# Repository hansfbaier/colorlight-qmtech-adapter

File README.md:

# colorlight-qmtech-adapter
Adapter to use Colorlight i5/i9 FPGA boards in a QMTech board form factor
This is the variant with Ethernet RJ45 connectors.

Please note:
* J1 Pin 8 is not length matched to the other Pins.
* J1 Pins 59 and 60 are not connected!

# Variants
* [With horizontal connector] (https://github.com/hansfbaier/colorlight-qmtech-adapter/)
* [With vertical connector] (https://github.com/hansfbaier/colorlight-qmtech-adapter/tree/upright-connector)

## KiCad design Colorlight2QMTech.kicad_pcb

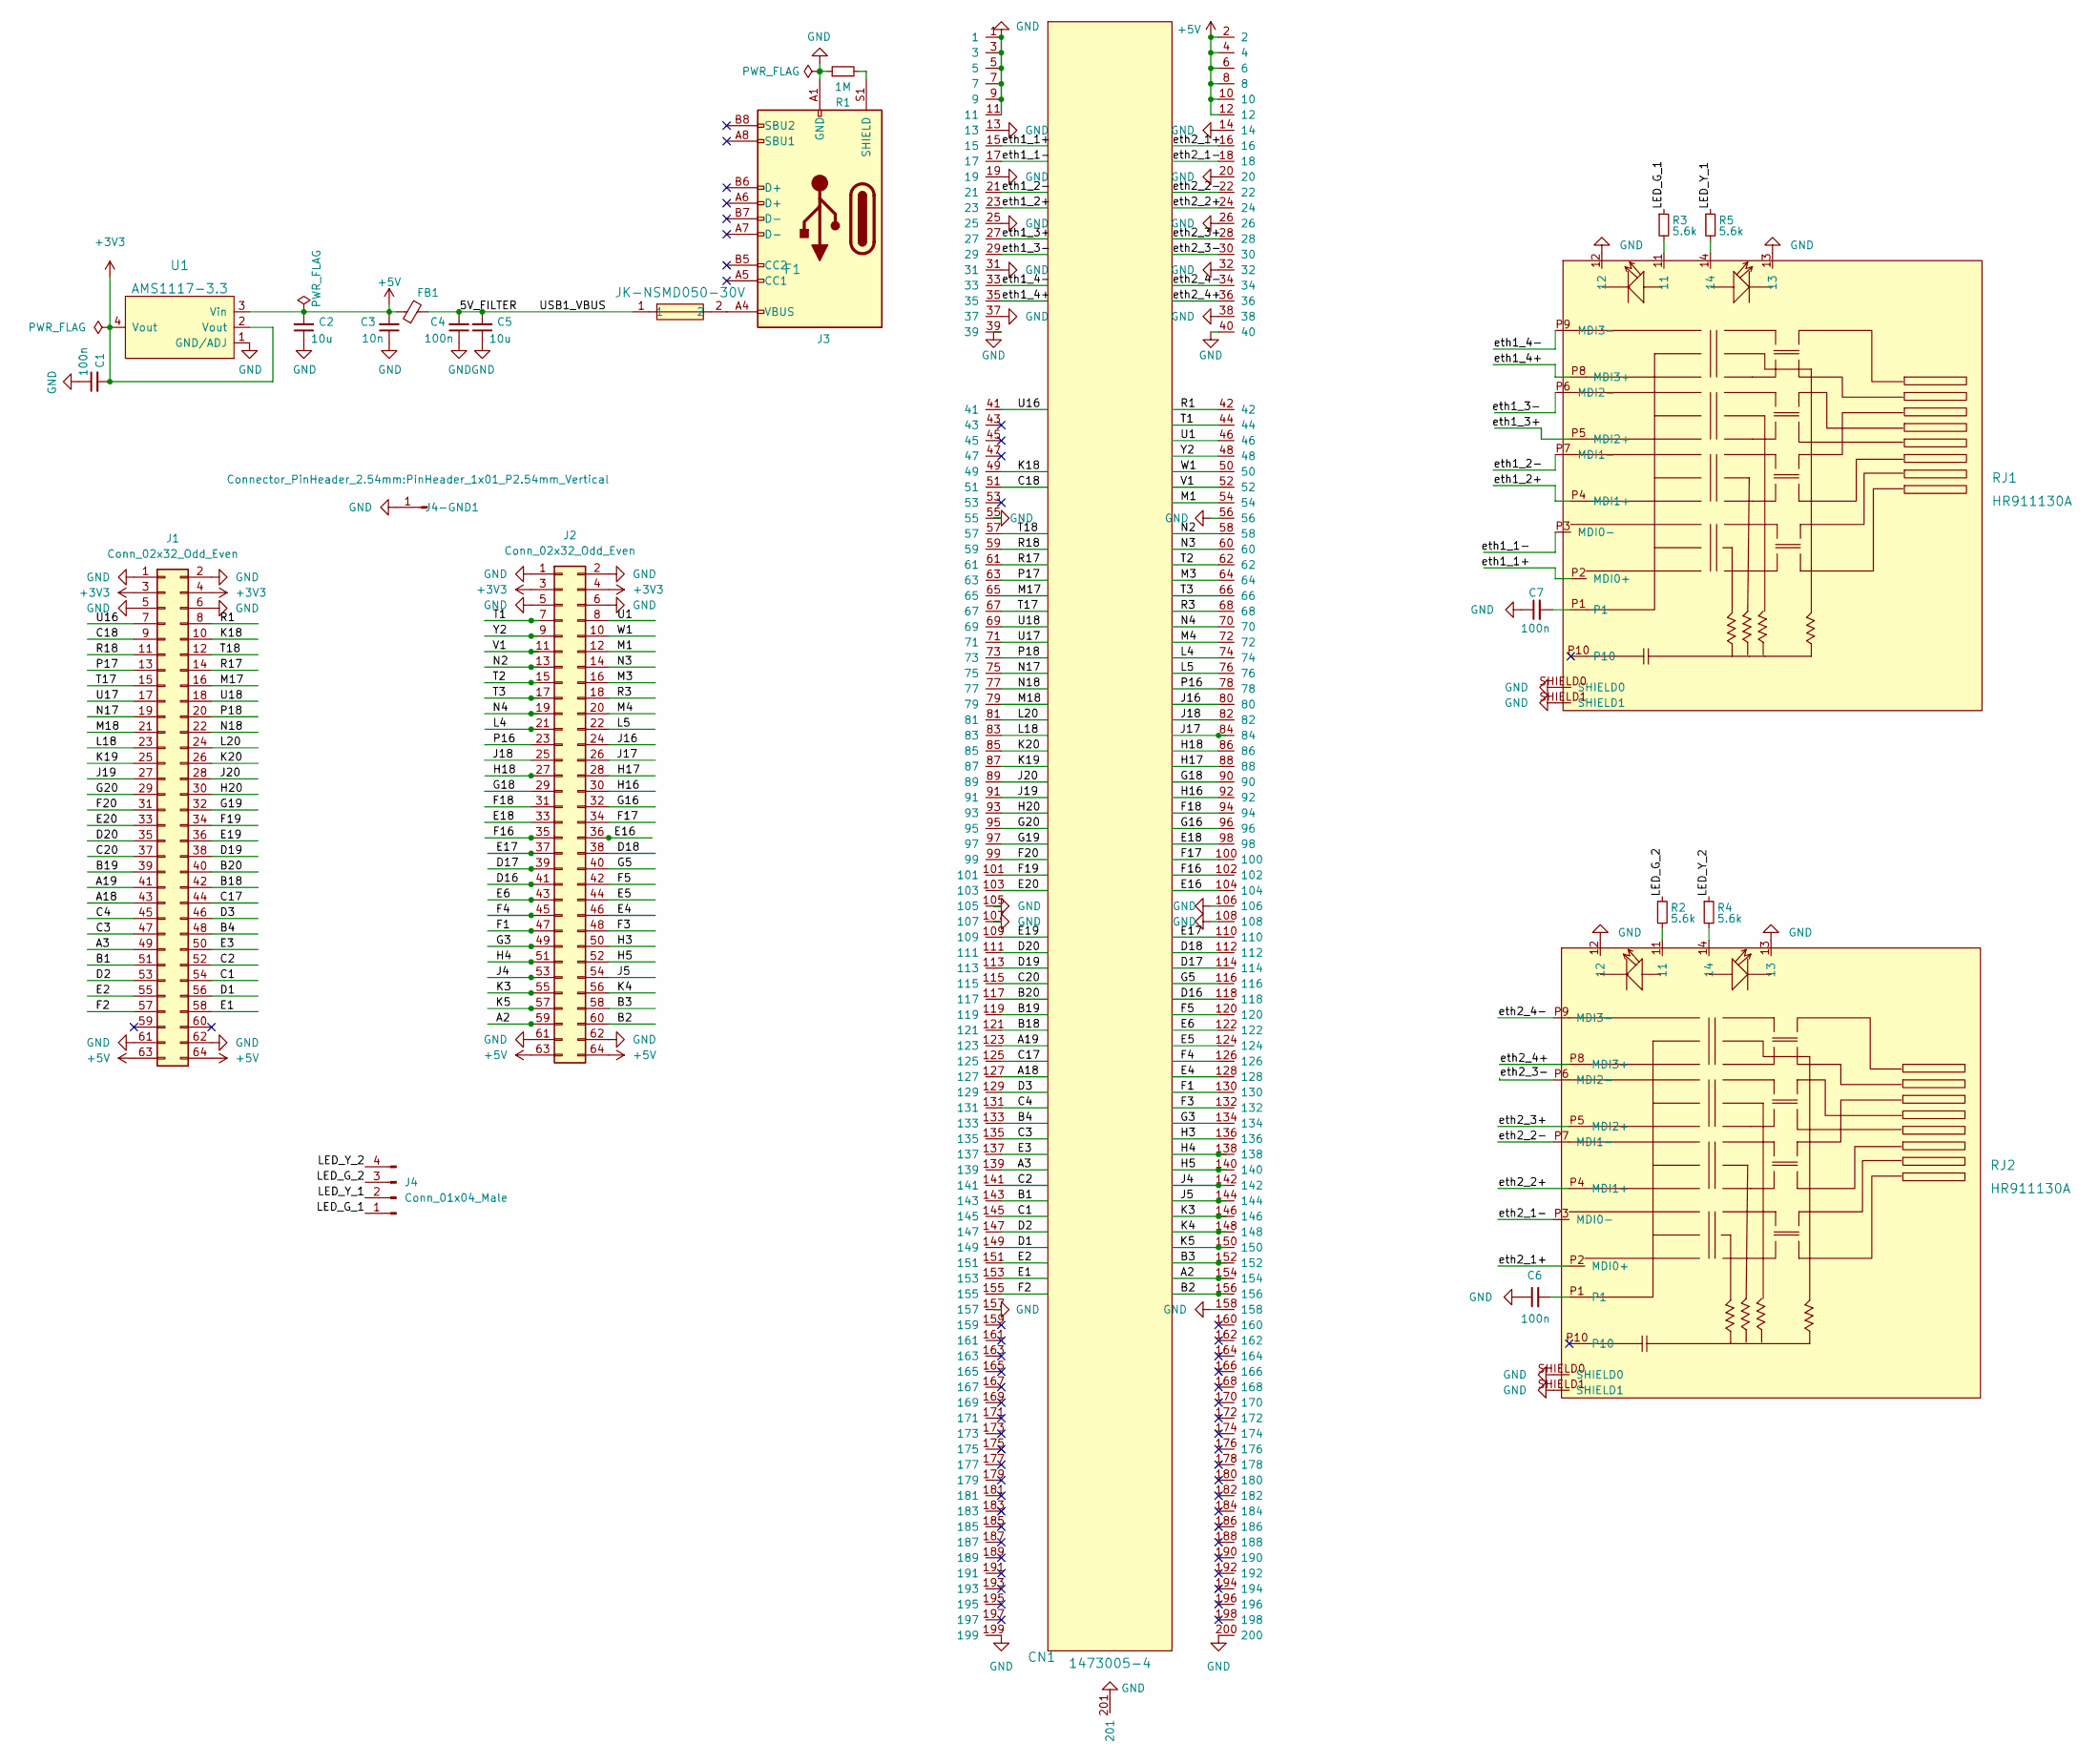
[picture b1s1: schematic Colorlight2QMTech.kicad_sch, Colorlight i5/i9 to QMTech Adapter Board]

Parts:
C1, C4, C6, C7: 100n; C_0603_1608Metric; LCSC C14663
C2, C5: 10u; C_0805_2012Metric; LCSC C15850
C3: 10n; C_0805_2012Metric; LCSC C1710
CN1: 1473005-4; SO-DIMM-SMD_200P-P0.60_1473005-4; LCSC Part C483268
F1: JK-NSMD050-30V; F1206; LCSC Part C720075
FB1: 2A; L_1206_3216Metric; LCSC C73732
J1, J2: Conn_02x32_Odd_Even; PinHeader_2x32_P2.54mm_Vertical
J3: Connector_USB_C_Receptacle_USB2.0; USB-C_SMD-TYPE-C-31-M-12; LCSC C165948
J4: Conn_01x04_Male
J4-GND1: Conn_01x01_Male; PinHeader_1x01_P2.54mm_Vertical
R1: 1M; R_0603_1608Metric; LCSC C22935
R2, R3, R4, R5: 5.6k; R_0603_1608Metric; LCSC C23189
RJ1, RJ2: HR911130A; RJ45-TH_HR911130A; LCSC Part C54408
U1: AMS1117-3.3; SOT-223-3_L6.5-W3.4-P2.30-LS7.0-BR; LCSC Part C6186

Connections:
+3V3: C1.2, J1.3, J1.4, J2.3, J2.4, U1.2 (Vout), U1.4 (Vout)
+5V: C2.2, C3.2, CN1.2, CN1.4, CN1.6, CN1.8, CN1.10, CN1.12, FB1.1, J1.63, J1.64, J2.63, J2.64, U1.3 (Vin)
/5V_FILTER: C4.2, C5.2, F1.1, FB1.2
/A2: CN1.154, J2.59
/A3: CN1.139, J1.49
/A18: CN1.127, J1.43
/A19: CN1.123, J1.41
/B1: CN1.143, J1.51
/B2: CN1.156, J2.60
/B3: CN1.152, J2.58
/B4: CN1.133, J1.48
/B18: CN1.121, J1.42
/B19: CN1.119, J1.39
/B20: CN1.117, J1.40
/C1: CN1.145, J1.54
/C2: CN1.141, J1.52
/C3: CN1.135, J1.47
/C4: CN1.131, J1.45
/C17: CN1.125, J1.44
/C18: CN1.51, J1.9
/C20: CN1.115, J1.37
/D1: CN1.149, J1.56
/D2: CN1.147, J1.53
/D3: CN1.129, J1.46
/D16: CN1.118, J2.41
/D17: CN1.114, J2.39
/D18: CN1.112, J2.38
/D19: CN1.113, J1.38
/D20: CN1.111, J1.35
/E1: CN1.153, J1.58
/E2: CN1.151, J1.55
/E3: CN1.137, J1.50
/E4: CN1.128, J2.46
/E5: CN1.124, J2.44
/E6: CN1.122, J2.43
/E16: CN1.104, J2.36
/E17: CN1.110, J2.37
/E18: CN1.98, J2.33
/E19: CN1.109, J1.36
/E20: CN1.103, J1.33
/F1: CN1.130, J2.47
/F2: CN1.155, J1.57
/F3: CN1.132, J2.48
/F4: CN1.126, J2.45
/F5: CN1.120, J2.42
/F16: CN1.102, J2.35
/F17: CN1.100, J2.34
/F18: CN1.94, J2.31
/F19: CN1.101, J1.34
/F20: CN1.99, J1.31
/G3: CN1.134, J2.49
/G5: CN1.116, J2.40
/G16: CN1.96, J2.32
/G18: CN1.90, J2.29
/G19: CN1.97, J1.32
/G20: CN1.95, J1.29
/H3: CN1.136, J2.50
/H4: CN1.138, J2.51
/H5: CN1.140, J2.52
/H16: CN1.92, J2.30
/H17: CN1.88, J2.28
/H18: CN1.86, J2.27
/H20: CN1.93, J1.30
/J4: CN1.142, J2.53
/J5: CN1.144, J2.54
/J16: CN1.80, J2.24
/J17: CN1.84, J2.26
/J18: CN1.82, J2.25
/J19: CN1.91, J1.27
/J20: CN1.89, J1.28
/K3: CN1.146, J2.55
/K4: CN1.148, J2.56
/K5: CN1.150, J2.57
/K18: CN1.49, J1.10
/K19: CN1.87, J1.25
/K20: CN1.85, J1.26
/L4: CN1.74, J2.21
/L5: CN1.76, J2.22
/L18: CN1.83, J1.23
/L20: CN1.81, J1.24
/LED_G_1: J4.1, R3.1
/LED_G_2: J4.3, R2.1
/LED_Y_1: J4.2, R5.1
/LED_Y_2: J4.4, R4.1
/M1: CN1.54, J2.12
/M3: CN1.64, J2.16
/M4: CN1.72, J2.20
/M17: CN1.65, J1.16
/M18: CN1.79, J1.21
/N2: CN1.58, J2.13
/N3: CN1.60, J2.14
/N4: CN1.70, J2.19
/N17: CN1.75, J1.19
/N18: CN1.77, J1.22
/P16: CN1.78, J2.23
/P17: CN1.63, J1.13
/P18: CN1.73, J1.20
/R1: CN1.42, J1.8
/R3: CN1.68, J2.18
/R17: CN1.61, J1.14
/R18: CN1.59, J1.11
/T1: CN1.44, J2.7
/T2: CN1.62, J2.15
/T3: CN1.66, J2.17
/T17: CN1.67, J1.15
/T18: CN1.57, J1.12
/U1: CN1.46, J2.8
/U16: CN1.41, J1.7
/U17: CN1.71, J1.17
/U18: CN1.69, J1.18
/V1: CN1.52, J2.11
/W1: CN1.50, J2.10
/Y2: CN1.48, J2.9
/eth1_1+: CN1.15, RJ1.P2 (MDI0+)
/eth1_1-: CN1.17, RJ1.P3 (MDI0-)
/eth1_2+: CN1.23, RJ1.P4 (MDI1+)
/eth1_2-: CN1.21, RJ1.P7 (MDI1-)
/eth1_3+: CN1.27, RJ1.P5 (MDI2+)
/eth1_3-: CN1.29, RJ1.P6 (MDI2-)
/eth1_4+: CN1.35, RJ1.P8 (MDI3+)
/eth1_4-: CN1.33, RJ1.P9 (MDI3-)
/eth2_1+: CN1.16, RJ2.P2 (MDI0+)
/eth2_1-: CN1.18, RJ2.P3 (MDI0-)
/eth2_2+: CN1.24, RJ2.P4 (MDI1+)
/eth2_2-: CN1.22, RJ2.P7 (MDI1-)
/eth2_3+: CN1.28, RJ2.P5 (MDI2+)
/eth2_3-: CN1.30, RJ2.P6 (MDI2-)
/eth2_4+: CN1.36, RJ2.P8 (MDI3+)
/eth2_4-: CN1.34, RJ2.P9 (MDI3-)
GND: C1.1, C2.1, C3.1, C4.1, C5.1, C6.1, C7.1, CN1.1, CN1.3, CN1.5, CN1.7, CN1.9, CN1.11, CN1.13, CN1.14, CN1.19, CN1.20, CN1.25, CN1.26, CN1.31, CN1.32, CN1.37, CN1.38, CN1.39, CN1.40, CN1.55, CN1.56, CN1.105, CN1.106, CN1.107, CN1.108, CN1.157, CN1.158, CN1.199, CN1.200, CN1.201, J1.1, J1.2, J1.5, J1.6, J1.61, J1.62, J2.1, J2.2, J2.5, J2.6, J2.61, J2.62, J3.A1 (GND), J3.A12 (GND), J3.B1 (GND), J3.B12 (GND), J4-GND1.1, R1.1, RJ1.12, RJ1.13, RJ1.SHIELD0, RJ1.SHIELD1, RJ2.12, RJ2.13, RJ2.SHIELD0, RJ2.SHIELD1, U1.1 (GND/ADJ)
unnamed: C6.2, RJ2.P1
unnamed: C7.2, RJ1.P1
unnamed: F1.2, J3.A4 (VBUS), J3.A9 (VBUS), J3.B4 (VBUS), J3.B9 (VBUS)
unnamed: J3.S1 (SHIELD), R1.2
unnamed: R2.2, RJ2.11
unnamed: R3.2, RJ1.11
unnamed: R4.2, RJ2.14
unnamed: R5.2, RJ1.14

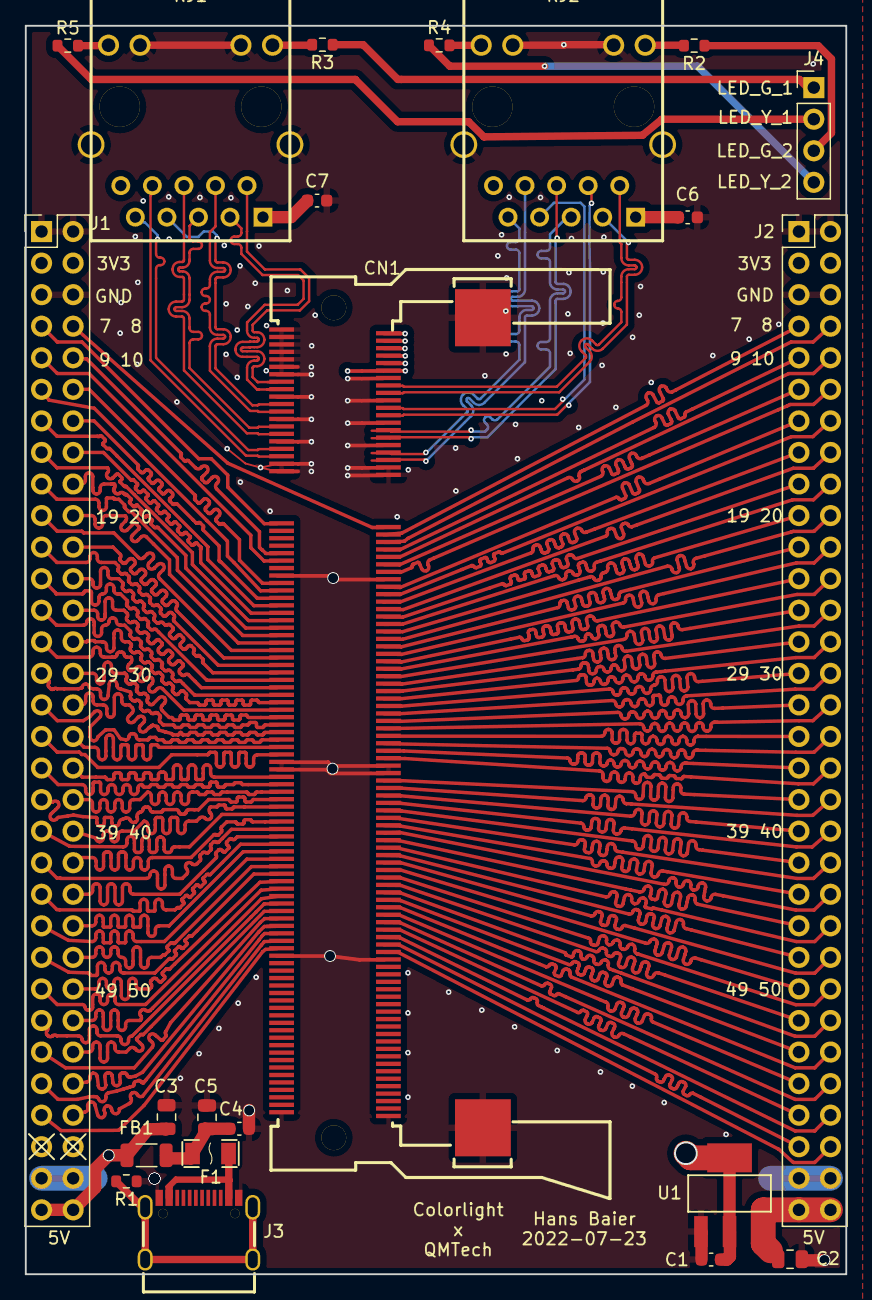
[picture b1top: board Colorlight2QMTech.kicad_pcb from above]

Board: 4 copper layers, 66.0 x 100.5 mm, 22 parts (0 on the bottom side), 138 nets.

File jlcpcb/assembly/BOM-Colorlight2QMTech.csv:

Comment,Designator,Footprint,LCSC
100n,"C1,C4,C6,C7",C_0603_1608Metric,C14663
10u,"C2,C5",C_0805_2012Metric,C15850
Connector_USB_C_Receptacle_USB2.0,J3,USB-C_SMD-TYPE-C-31-M-12,C165948
10n,C3,C_0805_2012Metric,C1710
1M,R1,R_0603_1608Metric,C22935
5.6k,"R2,R3,R4,R5",R_0603_1608Metric,C23189
1473005-4,CN1,SO-DIMM-SMD_200P-P0.60_1473005-4,C483268
HR911130A,"RJ1,RJ2",RJ45-TH_HR911130A,C54408
AMS1117-3.3,U1,SOT-223-3_L6.5-W3.4-P2.30-LS7.0-BR,C6186
JK-NSMD050-30V,F1,F1206,C720075
2A,FB1,L_1206_3216Metric,C73732
Conn_02x32_Odd_Even,J1,PinHeader_2x32_P2.54mm_Vertical,
Conn_02x32_Odd_Even,J2,PinHeader_2x32_P2.54mm_Vertical,
Conn_01x04_Male,J4,PinHeader_1x04_P2.54mm_Vertical,

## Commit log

2022-04-09 add README with image, LICENSE, .gitignore
2022-04-09 make headers face down in 3D view
2022-04-09 tidy schematic and export
2022-04-25 README: New screenshot and Notes
2022-04-25 New revision and first release: Fixed routing issues, better silk screen, break out ethernet signals.
2022-04-25 beautify schematic and export
2022-04-25 make alternate version with an upright connector
2022-04-26 add upright variant with ethernet connectors
2022-04-26 make board small enough to avoid engineering fee
2022-04-27 add LICENSE
2022-04-28 fix DRC track spacing
2022-04-28 make track widths a bit smaller to satisfy .105mm spacing
2022-04-29 remove unnecessary copper fill and fix silk screen
2022-07-23 add variant with horizontal SODIMM connector and ethernet
